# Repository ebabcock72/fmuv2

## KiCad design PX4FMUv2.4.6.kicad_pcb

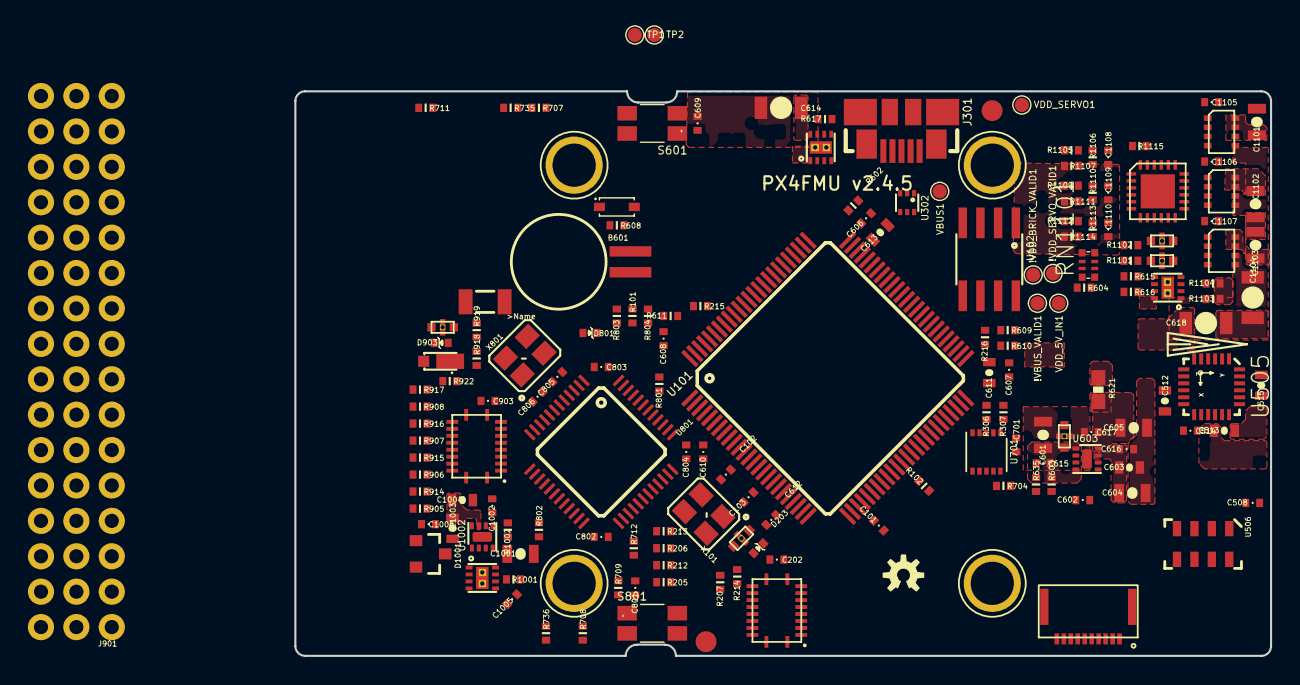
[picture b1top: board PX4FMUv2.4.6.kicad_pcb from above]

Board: 6 copper layers, 70.0 x 40.5 mm, 197 parts (0 on the bottom side), 161 nets, no tracks yet.

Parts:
!VBUS_VALID1: PAD.04; PAD.04X.04
!VDD_BRICK_VALID1: PAD.04; PAD.04X.04
!VDD_SERVO_VALID1: PAD.04; PAD.04X.04
ADC_PR1: PAD.04; PAD.04X.04
B601: MS621FE
C101, C202, C508, C514, C606, C607, C608, C609, C610, C612, C615, C616, C617, C701, C801, C802, C803, C804, C903, C1005, C1105, C1106, C1107: 0u1; 0402-CAP
C102, C103, C805, C806: 8p; 0402-CAP
C512, C513, C611, C613: 2u2; 0603-CAP
C515: 0u01; 0603-CAP
C601, C1001: 10u/25V; 0805-CAP
C602, C1002: 10n; 0402-CAP
C603, C1003: 1u; 0603-CAP
C604, C605, C1101, C1102, C1103: 22u/25V; 0805-CAP
C614, C618, C1104: 100u; 1206-CAP
C1004: 10u; 0603-CAP
C1008: 2u2; 0402-CAP
C1108, C1109, C1110: 10p/25V; 0402-CAP
CAN_H1: PAD.04; PAD.04X.04
CAN_L1: PAD.04; PAD.04X.04
D203, D801, D903: PESD0402-140; 0402-TVS
D602: RB751V40T1G; SOD323
D904: MSS1P4-M3; MICROSMP
D1001: PMEG2005CT; SOT23-3
F1001: 0ZCA0035FF2G; PTC-1206
FMU-BOOT1101: PAD.04; PAD.04X.04
GND1, GND.1: PAD.04; PAD.04X.04
IO-BOOT1101: PAD.04; PAD.04X.04
J203, J601: DF13C-6P-1.25V
J301: 47346-0001; MOLEX-47346-0001
J801: JST-ZH-3; JST-ZH-SMT-VERTICAL
J901: HEADER-3X163X16RA; 3X16RA
JP1, JP2: FIDUCIAL1.5X3; FIDUCIAL-1.5X3
L203, L603, L901, L1101, L1102: KNH16C104DA5TS; KYOCERA-KNH16-DA
LED701, LED703: AMBER; 0603-LED
LED702, LED704: GREEN; 0603-LED
LED705: BLUE; 0603-LED
M3_MOUNT1101, M3_MOUNT1102, M3_MOUNT1103, M3_MOUNT1104: MOUNT-HOLE3.1MM; MOUNT-HOLE3.1
OSHW_LOGO1: OSHW-LOGOS; OSHW-LOGO-S
R101: 470R; 0402-RES
R102, R603, R611, R615, R635, R704, R801, R802, R1002: 10K; 0402-RES
R205, R206, R207, R212, R213, R214, R215, R216: 120R; 0402-RES
R306, R307: 1K5; 0402-RES
R602, R604, R1103, R1104: 1M; 0402-RES
R608: 1K; 0402-RES
R609, R610, R918, R919, R922, R1101, R1102: 10K/0.1%; 0402-RES
R616: 25K5; 0402-RES
R617: 16K5; 0402-RES
R621: 220R; 0603-RES
R707, R708, R709, R711, R712, R735, R736, R803, R804, R905, R906, R907, R908, R914, R915, R916, R917: 220R; 0402-RES
R1001: 100K; 0402-RES
R1105, R1109, R1112: 453K; 0402-RES
R1106, R1110, R1113: 56K; 0402-RES
R1107, R1111, R1114: 105K; 0402-RES
R1115: 0R; 0402-RES
RN1101: 1M; EXB28V
S1RX1, S1TX1, S2RX1, S2TX1, S3RX1, S3TX1, S4RX1, S4TX1, S5_RX1, S5_TX1: PAD.04; PAD.04X.04
S601, S801: RESET; EVQP7J01K
TP1: i2c1_SCL; PAD.04X.04
TP2: i2c1_SDA; PAD.04X.04
U101: STM32F4X7VX; TQFP100
U102: FM25V01; SO08
U202, U902: TXS0108QFN20; QFN20-RGY
U302: NUF2042XV6; SOT563-6
U505: MPU-6000; QFN-24
U506: MS5611-01BA
U601, U602: BQ24315; QFN8-DSG
U603, U1002: MIC5332; MLF-8-EPAD
U701: TCA62724FMG; SON10
U703: LRTB GFTG-T7AW-1+V7A7-29+R5T9-49-L; 6-PLCC
U801: STM32F10XCXT6; TQFP48
U1001: BQ24313; QFN8-DSG
U1101: LTC4417; MO-220
U1102, U1103, U1104: NTHD4102PT1G; 1206-8
VBUS1: PAD.04; PAD.04X.04
VDDA_3V1101: PAD.04; PAD.04X.04
VDD_3V1101, VDD_5V_BRICK1, VDD_5V_IN1: PAD.04; PAD.04X.04
VDD_SERVO1: PAD.04; PAD.04X.04
X101, X801: 3.2x2.5 mm / 24 MHz / 15 ppm; OSCILLATOR-3.2X2.5
X503: 0512811094; 51281-1094

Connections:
/PX4FMUv2.4.6_1/FRAM_MISO: U101.53, U102.2
/PX4FMUv2.4.6_1/FRAM_MOSI: U101.54, U102.5
/PX4FMUv2.4.6_1/FRAM_SCK: U101.52, U102.6
/PX4FMUv2.4.6_1/~FRAM_CS: U101.57, U102.1
/PX4FMUv2.4.6_8/IO-USART1_RX: J801.P$3, U801.31
ACCEL_DRDY: U101.90, X503.3
BATT_CURRENT_SENS: R1101.P$1, U101.26
BATT_VOLTAGE_SENS: R1102.P$1, U101.25
CAN2_RX: R216.P$1, U101.51
CAN2_TX: R215.P$1, U101.92
FMU-BOOT0: FMU-BOOT1101.P$1, R611.P$2, U101.94
FMU-I2C1_SCL: TP1.P$1, U101.95
FMU-I2C1_SDA: TP2.P$1, U101.96
FMU-I2C2_SCL: R306.P$1, U101.47, U701.3
FMU-I2C2_SDA: R307.P$1, U101.48, U701.2
FMU-UART4_RX: U101.24, U202.8
FMU-UART4_TX: U101.23, U202.9
FMU-UART7_RX: U101.38, U202.4
FMU-UART7_TX: U101.39, U202.5
FMU-UART8_RX: U101.97, U202.6
FMU-UART8_TX: U101.98, U202.7
FMU-VDD_3V3: C101.P$1, C202.P$1, C603.P$1, C604.P$1, C606.P$1, C607.P$1, C608.P$1, C610.P$1, C612.P$1, C616.P$1, C701.P$1, D602.A, R306.P$2, R307.P$2, R602.P$2, R604.P$2, U101.11, U101.19, U101.21, U101.22, U101.28, U101.50, U101.75, U101.100, U102.3, U102.7, U102.8, U202.2, U202.10, U202.19, U603.7, U701.1, U701.10, VDD_3V1101.P$1
FMU-~RESET: C609.P$2, R635.P$1, S601.A1, U101.14, U603.3, U701.4
GND: B601.2, C101.P$2, C102.P$2, C103.P$1, C202.P$2, C508.P$2, C512.P$2, C513.P$2, C514.P$2, C515.P$2, C601.P$2, C602.P$1, C603.P$2, C604.P$2, C605.P$2, C606.P$2, C607.P$2, C608.P$2, C609.P$1, C610.P$2, C611.P$2, C612.P$2, C613.P$2, C614.P$2, C615.P$2, C616.P$2, C617.P$2, C618.P$2, C701.P$2, C801.P$1, C802.P$2, C803.P$2, C804.P$2, C805.P$2, C806.P$1, C903.P$2, C1001.P$2, C1002.P$2, C1003.P$2, C1004.P$2, C1005.P$2, C1008.P$2, C1101.P$2, C1102.P$2, C1103.P$2, C1104.P$2, C1105.P$2, C1106.P$2, C1107.P$2, C1108.P$2, C1109.P$2, C1110.P$2, D203.A, D801.A, D903.A, GND1.P$1, GND.1.P$1, J203.6, J301.GND, J301.GND1, J301.GND2, J301.GND3, J301.GND4, J601.5, J601.6, J801.P$2, L203.P$3, L203.P$4, L203.P$5, L603.P$3, L603.P$4, L603.P$5, L901.P$3, L901.P$4, L901.P$5, L1101.P$3, L1101.P$4, L1101.P$5, L1102.P$3, L1102.P$4, L1102.P$5, R102.P$2, R610.P$2, R611.P$1, R615.P$2, R616.P$2, R617.P$2, R621.1, R704.P$1, R708.P$1, R711.P$1, R801.P$2, R802.P$2, R919.P$1, R1001.P$1, R1002.P$1, R1103.P$2, R1104.P$2, R1107.P$2, R1111.P$2, R1114.P$2, R1115.P$1, S601.B3, S801.B3, U101.10, U101.20, U101.27, U101.74, U101.99, U102.4, U202.11, U302.2, U505.1, U505.18, U506.2, U506.3, U601.2, U601.6, U601.GND, U601.P$2, U601.P$3, U602.2, U602.6, U602.GND, U602.P$2, U602.P$3, U603.2, U603.GND, U701.5, U801.8, U801.23, U801.35, U801.47, U902.11, U1001.2, U1001.5, U1001.6, U1001.GND, U1001.P$2, U1001.P$3, U1002.2, U1002.GND, U1101.P$10, U1101.P$25, X101.2, X101.4, X503.2, X801.2, X801.4
GYRO_DRDY: U101.35, X503.5
IO-BOOT0: IO-BOOT1101.P$1, R801.P$1, U801.44
IO-CH1: U801.10, U902.9
IO-CH2: U801.11, U902.8
IO-CH3: U801.45, U902.7
IO-CH4: U801.46, U902.6
IO-CH5: U801.16, U902.5
IO-CH6: U801.17, U902.4
IO-CH7: U801.18, U902.3
IO-CH8: U801.19, U902.1
IO-USART1_TX: R101.P$2, U801.30
IO-VDD_3V3: C802.P$1, C803.P$1, C804.P$1, C903.P$1, C1003.P$1, C1004.P$1, U801.9, U801.24, U801.36, U801.48, U902.2, U902.10, U902.19, U1002.7
IO-VDD_5V5: C1001.P$1, C1005.P$1, D1001.3, J901.2, LED702.A, LED703.A, LED705.A, U1002.1, U1002.4
IO-~RESET: C801.P$2, S801.A1, U801.7, U1002.3
IO-~VDD_SERVO_IN_FAULT: U801.38, U1001.4
MAG_DRDY: U101.36, X503.4
MPU_DRDY: U101.62, U505.12
unnamed: C102.P$1, U101.12, X101.3
unnamed: C103.P$2, U101.13, X101.1
unnamed: C512.P$1, U505.10
unnamed: C515.P$1, U505.20
unnamed: C601.P$1, C615.P$1, L603.P$2, R603.P$1, U603.1, U603.4
unnamed: C602.P$2, U603.6
unnamed: C611.P$1, U101.49
unnamed: C613.P$1, U101.73
unnamed: C805.P$1, U801.5, X801.3
unnamed: C806.P$2, U801.6, X801.1
unnamed: C1002.P$1, U1002.6
unnamed: C1105.P$1, U1101.P$18, U1102.P$1, U1102.P$3
unnamed: C1106.P$1, U1101.P$16, U1103.P$1, U1103.P$3
unnamed: C1107.P$1, U1101.P$14, U1104.P$1, U1104.P$3
unnamed: C1108.P$1, R1105.P$2, R1106.P$1, U1101.P$1
unnamed: C1109.P$1, R1109.P$2, R1110.P$1, U1101.P$3
unnamed: C1110.P$1, R1112.P$2, R1113.P$1, U1101.P$5
unnamed: D203.C, J203.1, L203.P$2
unnamed: D602.C, R608.P$2
unnamed: D903.C, D904.CATHODE, L901.P$1
unnamed: D1001.1, F1001.2
unnamed: D1001.2, U1001.8
unnamed: J203.4, R215.P$2
unnamed: J203.5, R216.P$2
unnamed: J301.D+, U302.3
unnamed: J301.D-, U302.1
unnamed: J601.3, L1101.P$1, R1104.P$1
unnamed: J601.4, L1102.P$1, R1103.P$1
unnamed: J901.7, R905.P$2
unnamed: J901.10, R914.P$2
unnamed: J901.13, R906.P$2
unnamed: J901.16, R915.P$2
unnamed: J901.19, R907.P$2
unnamed: J901.22, R916.P$2
unnamed: J901.25, R908.P$2
unnamed: J901.28, R917.P$2
unnamed: L1101.P$2, R1101.P$2
unnamed: L1102.P$2, R1102.P$2
unnamed: LED701.C, R735.P$2
unnamed: LED702.C, R708.P$2
unnamed: LED703.C, R736.P$2
unnamed: LED704.C, R711.P$2
unnamed: LED705.C, R712.P$2
unnamed: R101.P$1, U101.69
unnamed: R102.P$1, U101.37
unnamed: R205.P$1, U202.17
unnamed: R206.P$1, U202.15
unnamed: R207.P$1, U202.13
unnamed: R212.P$1, U202.16
unnamed: R213.P$1, U202.14
unnamed: R214.P$1, U202.12
unnamed: R616.P$1, U602.7
unnamed: R617.P$1, U601.7
unnamed: R704.P$2, U701.6
unnamed: R707.P$2, R735.P$1
unnamed: R709.P$2, R736.P$1
unnamed: R802.P$1, U801.20
unnamed: R803.P$1, U801.12
unnamed: R804.P$1, U801.13
unnamed: R905.P$1, U902.20
unnamed: R906.P$1, U902.17
unnamed: R907.P$1, U902.15
unnamed: R908.P$1, U902.13
unnamed: R914.P$1, U902.18
unnamed: R915.P$1, U902.16
unnamed: R916.P$1, U902.14
unnamed: R917.P$1, U902.12
unnamed: R918.P$2, R922.P$1
unnamed: R1001.P$2, U1001.7
unnamed: R1106.P$2, R1107.P$1, U1101.P$2
unnamed: R1110.P$2, R1111.P$1, U1101.P$4
unnamed: R1113.P$2, R1114.P$1, U1101.P$6
unnamed: R1115.P$2, U1101.P$24
unnamed: U701.7, U703.C3
unnamed: U701.8, U703.C2
unnamed: U701.9, U703.C1
unnamed: U1101.P$13, U1104.P$2, U1104.P$4
unnamed: U1101.P$15, U1103.P$2, U1103.P$4
unnamed: U1101.P$17, U1102.P$2, U1102.P$4
OTG_FS_DM: U101.70, U302.6
OTG_FS_DP: U101.71, U302.4
RSSI_IN: U801.15, U801.33
SERIAL3_RX: J203.3, R207.P$2, S3RX1.P$1
SERIAL3_TX: J203.2, R214.P$2, S3TX1.P$1
SERIAL4_RX: R206.P$2, S4RX1.P$1
SERIAL4_TX: R213.P$2, S4TX1.P$1
SERIAL5_RX: R205.P$2, S5_RX1.P$1
SERIAL5_TX: R212.P$2, S5_TX1.P$1
SERIAL_FMU_TO_IO: R804.P$2, U101.63
SERIAL_IO_TO_FMU: R803.P$2, U101.64
SPI_INT_MISO: U101.31, U505.9, U506.6, X503.9
SPI_INT_MOSI: U101.32, U505.24, U506.7, X503.8
SPI_INT_SCK: U101.30, U505.23, U506.8, X503.10
VBAT: B601.1, R608.P$1, U101.6, U801.1
VBUS: C1103.P$1, J301.VBUS, R1112.P$1, U101.68, U302.5, U1101.P$19, U1104.P$7, U1104.P$8, VBUS1.P$1
VDD_3V3_SENSORS: C508.P$1, C513.P$1, C514.P$1, C605.P$1, C617.P$1, R621.2, U505.13, U506.1, U603.8, VDDA_3V1101.P$1, X503.1
VDD_3V3_SENSORS_EN: R603.P$2, R635.P$2, U101.2, U603.5
VDD_3V3_SPEKTRUM: C1008.P$1, D801.C, J801.P$1, U1002.8
VDD_3V3_SPEKTRUM_EN: R1002.P$2, U801.2, U1002.5
VDD_5V_BRICK: C1101.P$1, J601.1, J601.2, R1105.P$1, U1101.P$21, U1102.P$7, U1102.P$8, VDD_5V_BRICK1.P$1
VDD_5V_HIPOWER: C614.P$1, U601.8
VDD_5V_IN: C1104.P$1, F1001.1, L603.P$1, LED701.A, LED704.A, R609.P$2, RN1101.5, RN1101.6, RN1101.7, U601.1, U602.1, U703.A1, U703.A2, U703.A3, U1101.P$12, U1102.P$5, U1102.P$6, U1103.P$5, U1103.P$6, U1104.P$5, U1104.P$6, VDD_5V_IN1.P$1
VDD_5V_PERIPH: C618.P$1, L203.P$1, U602.8
VDD_5V_SENS: R609.P$1, R610.P$1, U101.29
VDD_SERVO: C1102.P$1, D904.ANODE, J901.5, J901.8, J901.11, J901.14, J901.17, J901.20, J901.23, J901.26, J901.29, J901.32, J901.35, J901.38, J901.41, J901.44, J901.47, R922.P$2, R1109.P$1, U1101.P$20, U1103.P$7, U1103.P$8, VDD_SERVO1.P$1
VDD_SERVO_IN: L901.P$2, U1001.1
VDD_SERVO_SENS: R918.P$1, R919.P$2, U801.14
~ACCEL_MAG_CS: U101.9, X503.6
~BARO_CS: U101.88, U506.5
~FMU-LED_AMBER: R707.P$1, U101.43
~GYRO_CS: U101.7, X503.7
~IO-LED_AMBER: R709.P$1, U801.28
~IO-LED_BLUE: R712.P$1, U801.27
~MPU_CS: U101.17, U505.8
~VBUS_VALID: !VBUS_VALID1.P$1, RN1101.2, U101.15, U1101.P$9
~VDD_5V_HIPOWER_OC: R602.P$1, U101.41, U601.4
~VDD_5V_PERIPH_EN: R615.P$1, U101.67, U601.5, U602.5
~VDD_5V_PERIPH_OC: R604.P$1, U101.46, U602.4
~VDD_BRICK_VALID: !VDD_BRICK_VALID1.P$1, RN1101.4, U101.91, U1101.P$7
~VDD_SERVO_VALID: !VDD_SERVO_VALID1.P$1, RN1101.3, U101.93, U1101.P$8

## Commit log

2018-12-11 initial eagle files
2018-12-12 moved to sub directory
2018-12-12 Initial conversion from eagle to kicad
2018-12-17 kicad files uploaded
2018-12-18 removed some things
2018-12-18 removed more things

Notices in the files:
PX4FMUv2.4.6.kicad_pcb:
(c) 2013 mjs/lm/jo
